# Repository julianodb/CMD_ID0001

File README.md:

CMD_ID0001_SW_1
===============
SW_1 : Health Manager implementation ofr test purposes. Uses de IEEE 11073 protocol (20601)

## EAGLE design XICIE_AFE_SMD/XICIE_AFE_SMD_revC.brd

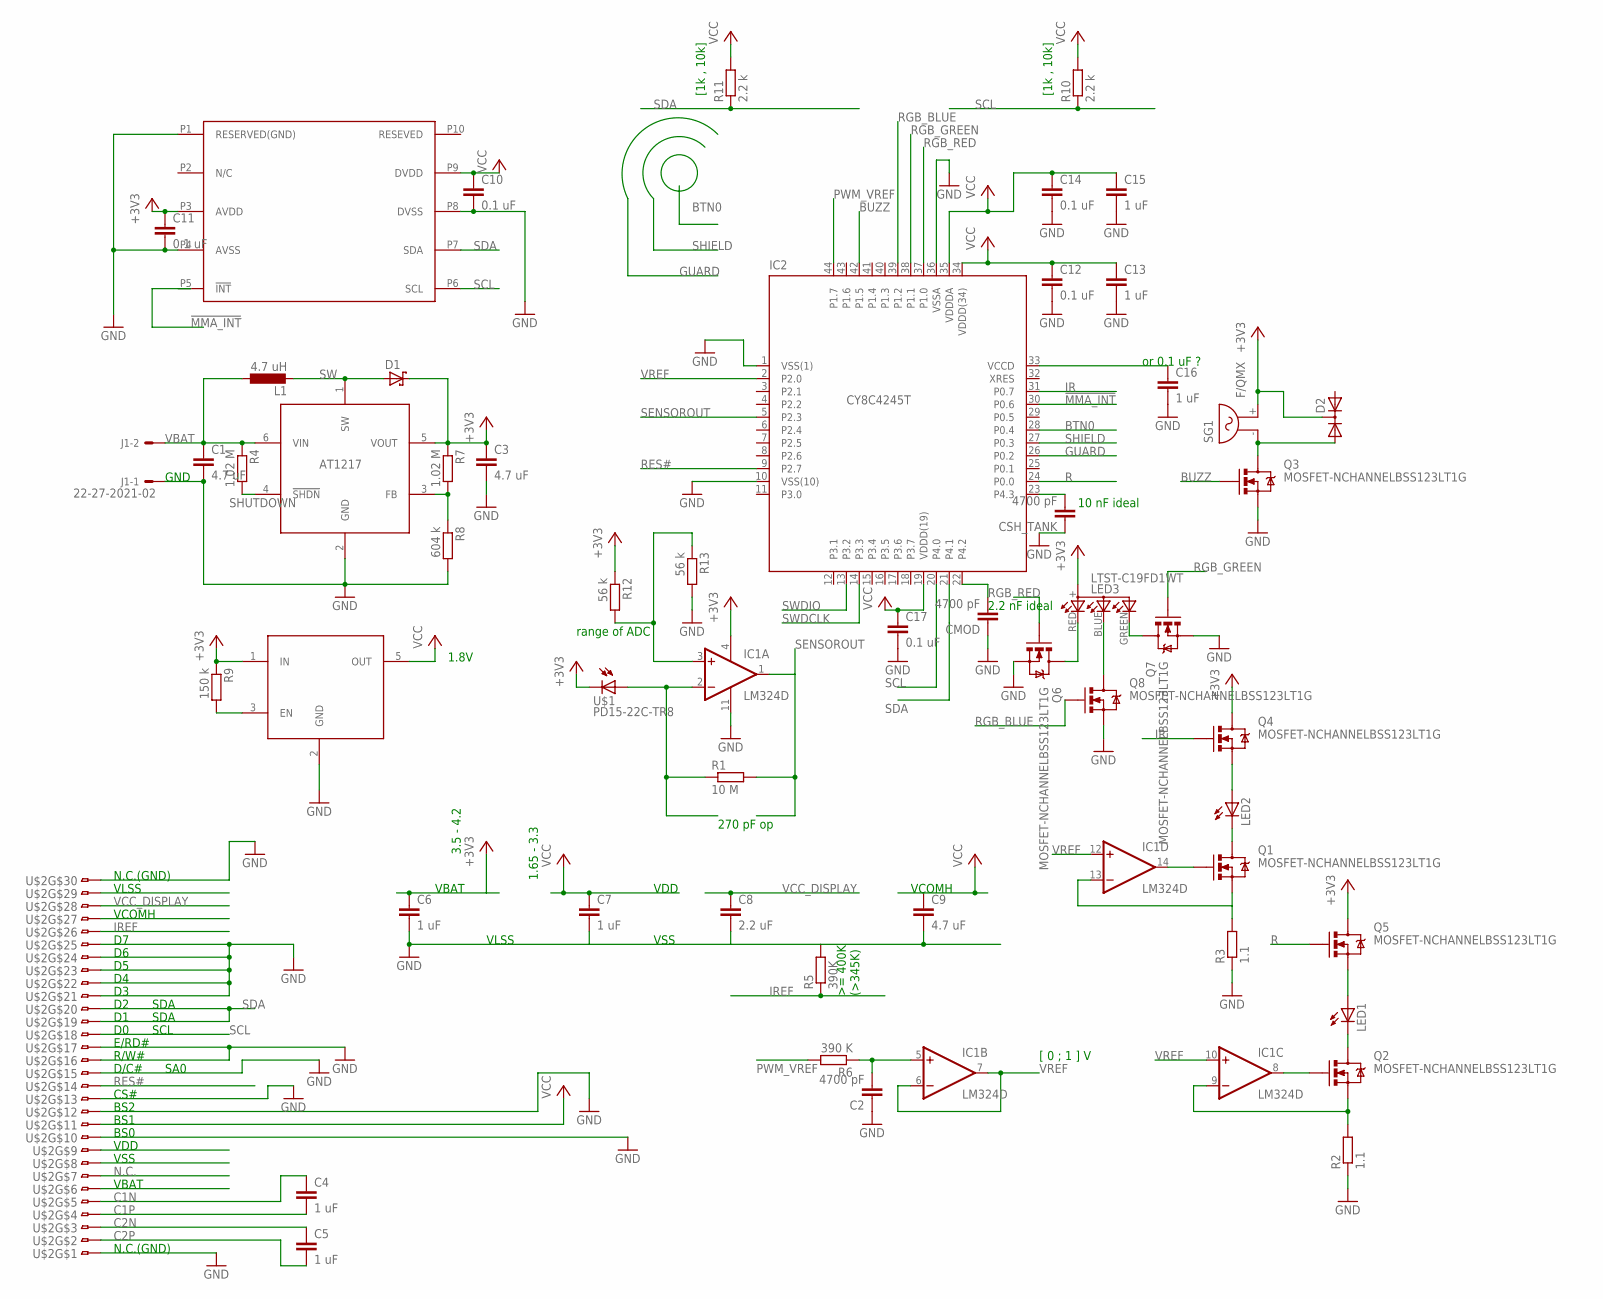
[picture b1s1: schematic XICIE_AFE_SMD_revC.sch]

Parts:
C1, C3, C9: 4.7 uF; C0603
C2: 4700 pF; C0402
C4, C5, C6, C7, C13, C15, C16: 1 uF; C0402
C8: 2.2 uF; C0603
C10, C11, C12, C14, C17: 0.1 uF; C0402
CMOD: 4700 pF; C0402
CSH_TANK: 4700 pF; C0402
D1: SCHOTTKY-DIODESMD; SMINI2-F5-B
D2: DIODE-2AC|CASOT23; SOT23
IC1: LM324D; SO14
IC2: CY8C4245T; TQFP44
IC3: AAT1217; SOT23-6
J1: 22-27-2021-02; 6410-02
L1: 4.7 uH; L2518
LED1, LED2: LED5MM
LED3: LTST-C19FD1WT; GM1WA55311A
Q1, Q2, Q3, Q4, Q5, Q6, Q7, Q8: MOSFET-NCHANNELBSS123LT1G; SOT23
R1: 10 M; R0402
R2, R3: 1.1; R0402
R4, R7: 1.02 M; R0805
R5: 390K; R0603
R6: 390 K; R0603
R8: 604 k; R0603
R9: 150 k; R0603
R10, R11: 2.2 k; R0402
R12, R13: 56 k; R0603
SG1: F/QMX
U$1: PD15-22C-TR8; PHOTO_SMD
U$2: ER-OLED0.96; FLEX0.7X30
U$3: AAT3221; SOT23-5
U$4: MMA7660FC; DFN10

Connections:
!MMA_INT: IC2.30 (P0.6)
+3V3: C3.1, C6.1, C11.1, D1.C, D2.3 (C), IC1.4 (V+), IC3.5 (VOUT), LED3.+ (A), Q4.3 (D), Q5.3 (D), R7.1, R9.1, R12.1, SG1.+ (2), U$1.CATHODE1 (C), U$1.CATHODE2 (C), U$2.P6, U$3.1 (IN), U$4.P3 (AVDD)
BTN0: IC2.28 (P0.4)
BUZZ: IC2.42 (P1.5), Q3.1 (G)
C1N: C4.1, U$2.P5
C1P: C4.2, U$2.P4
C2N: C5.1, U$2.P3
C2P: C5.2, U$2.P2
GND: C1.2, C2.1, C3.2, C6.2, C7.2, C8.2, C9.2, C10.2, C11.2, C12.2, C13.2, C14.2, C15.2, C16.2, C17.2, CMOD.1, CSH_TANK.1, IC1.11 (V-), IC2.1 (VSS(1)), IC2.10 (VSS(10)), IC2.36 (VSSA), IC3.2 (GND), J1.1, Q3.2 (S), Q6.2 (S), Q7.2 (S), Q8.2 (S), R2.1, R3.1, R5.2, R8.2, R13.2, U$2.P1, U$2.P8, U$2.P10, U$2.P12, U$2.P13, U$2.P15, U$2.P16, U$2.P17, U$2.P21, U$2.P22, U$2.P23, U$2.P24, U$2.P25, U$2.P29, U$2.P30, U$3.2 (GND), U$4.P1 (RESERVED(GND)), U$4.P4 (AVSS), U$4.P8 (DVSS)
GUARD: IC2.26 (P0.2)
IR: IC2.31 (P0.7), Q4.1 (G)
IREF: R5.1, U$2.P26
unnamed: IC1.2 (-IN), R1.1, U$1.ANODE1 (A), U$1.ANODE2 (A)
unnamed: IC1.9 (-IN), Q2.2 (S), R2.2
unnamed: LED2.A, Q4.2 (S)
unnamed: LED1.K (C), Q2.3 (D)
unnamed: LED2.K (C), Q1.3 (D)
unnamed: IC1.8 (OUT), Q2.1 (G)
unnamed: IC1.13 (-IN), Q1.2 (S), R3.2
unnamed: C2.2, IC1.5 (+IN), R6.1
unnamed: C16.1, IC2.33 (VCCD)
unnamed: IC3.3 (FB), R7.2, R8.1
unnamed: D2.1 (A1), Q3.3 (D), SG1.- (1)
unnamed: R9.2, U$3.3 (EN)
unnamed: IC1.3 (+IN), R12.2, R13.1
unnamed: LED1.A, Q5.2 (S)
unnamed: LED3.RED (CRED), Q6.3 (D)
unnamed: LED3.BLUE (CBLUE), Q8.3 (D)
unnamed: IC1.14 (OUT), Q1.1 (G)
unnamed: LED3.GREEN (CGREEN), Q7.3 (D)
unnamed: CMOD.2, IC2.22 (P4.2)
unnamed: CSH_TANK.2, IC2.23 (P4.3)
N.C.: U$2.P7
P2.2: IC2.4 (P2.2)
P2.6: IC2.8 (P2.6)
P3.6: IC2.17 (P3.6)
PWM_VREF: IC2.44 (P1.7), R6.2
R: IC2.24 (P0.0), Q5.1 (G)
RES#: IC2.9 (P2.7), U$2.P14
RGB_BLUE: IC2.39 (P1.2), Q8.1 (G)
RGB_GREEN: IC2.38 (P1.1), Q7.1 (G)
RGB_RED: IC2.37 (P1.0), Q6.1 (G)
SCL: IC2.20 (P4.0), R10.1, U$2.P18, U$4.P6 (SCL)
SDA: IC2.21 (P4.1), R11.1, U$2.P19, U$2.P20, U$4.P7 (SDA)
SENSOROUT: IC1.1 (OUT), IC2.5 (P2.3), R1.2
SHIELD: IC2.27 (P0.3)
SHUTDOWN: IC3.4 (!SHDN), R4.2
SW: D1.A, IC3.1 (SW), L1.2
SWDCLK: IC2.14 (P3.3)
SWDIO: IC2.13 (P3.2)
VBAT: C1.1, IC3.6 (VIN), J1.2, L1.1, R4.1
VCC: C7.1, C9.1, C10.1, C12.1, C13.1, C14.1, C15.1, C17.1, IC2.19 (VDDD(19)), IC2.34 (VDDD(34)), IC2.35 (VDDDA), R10.2, R11.2, U$2.P9, U$2.P11, U$2.P27, U$3.5 (OUT), U$4.P9 (DVDD)
VCC_DISPLAY: C8.1, U$2.P28
VREF: IC1.6 (-IN), IC1.7 (OUT), IC1.10 (+IN), IC1.12 (+IN), IC2.2 (P2.0)

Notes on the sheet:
270 pF op
GND
BS0
BS1
BS2
N.C.(GND)
VBAT
VSS
VLSS
VCOMH
3.5 - 4.2
1.65 - 3.3
VDD
1.8V
SA0
SDA
SCL
[1k , 10k]
range of ADC
[ 0 ; 1 ] V
CS#
2.2 nF ideal
10 nF ideal
D/C#
E/RD#
R/W#
or 0.1 uF ?

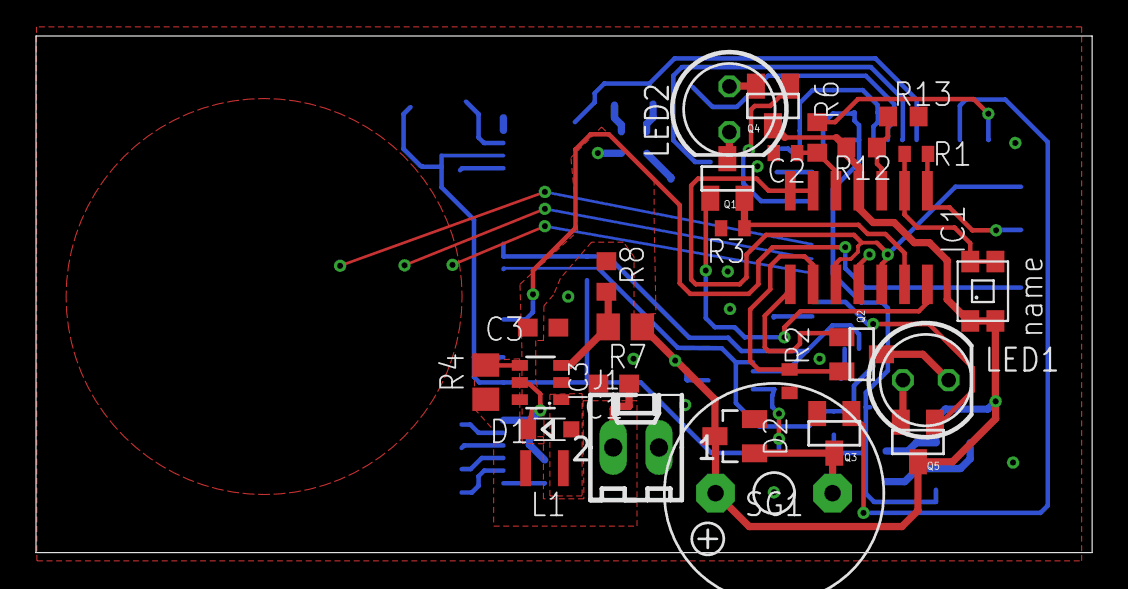
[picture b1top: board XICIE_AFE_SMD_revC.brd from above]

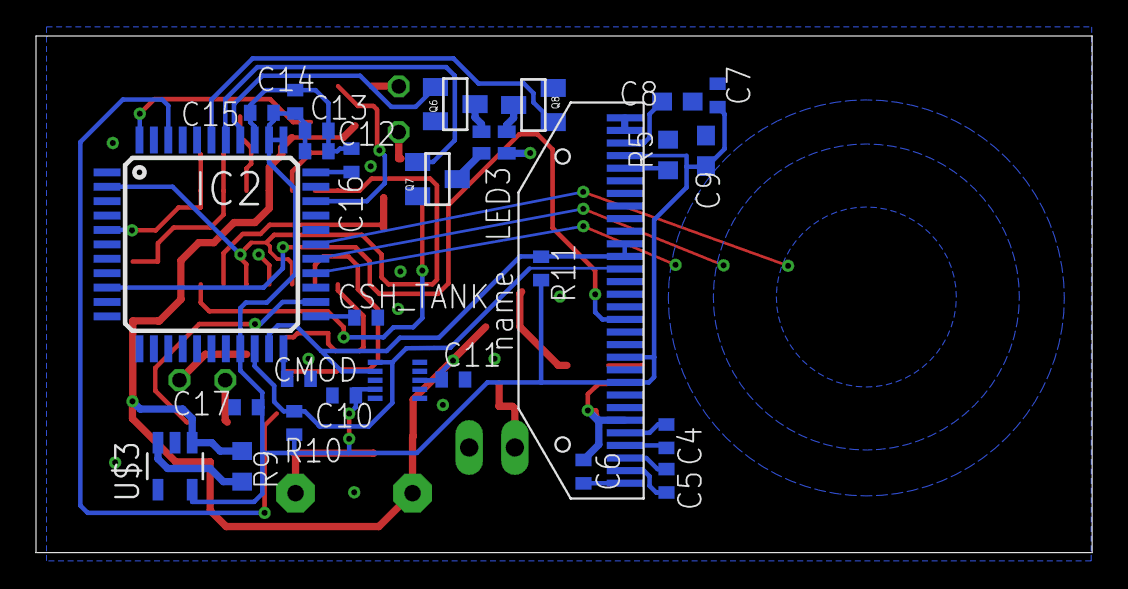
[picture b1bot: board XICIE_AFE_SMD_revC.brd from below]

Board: 2 copper layers, 58.7 x 28.7 mm, 55 parts (28 on the bottom side), 44 nets.

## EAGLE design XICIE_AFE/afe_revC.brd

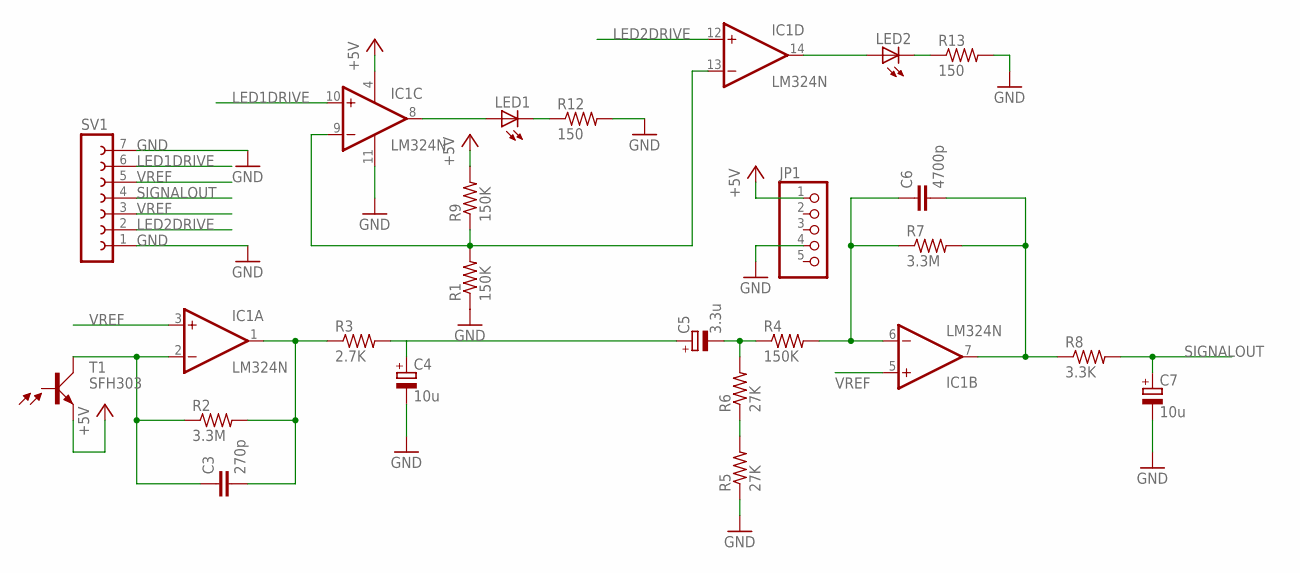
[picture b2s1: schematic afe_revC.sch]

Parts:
C3: 270p; C050-024X044
C4, C7: 10u; E2,5-5
C5: 3.3u; E2,5-5
C6: 4700p; C050-024X044
IC1: LM324N; DIL14
JP1: PINHD-1X5; 1X05
LED1, LED2: LED5MM
R1, R4, R9: 150K; 0207/10
R2, R7: 3.3M; 0207/10
R3: 2.7K; 0207/10
R5, R6: 27K; 0207/10
R8: 3.3K; 0207/10
R12, R13: 150; 0207/10
SV1: FE07-1; FE07
T1: SFH303

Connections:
+5V: IC1.4 (V+), JP1.1, R9.2, T1.1 (E)
GND: C4.-, C7.-, IC1.11 (V-), JP1.4, R1.1, R5.1, R12.2, R13.2, SV1.1, SV1.7
LED1DRIVE: IC1.10 (+IN), SV1.6
LED2DRIVE: IC1.12 (+IN), SV1.2
unnamed: C3.2, IC1.1 (OUT), R2.2, R3.1
unnamed: C3.1, IC1.2 (-IN), R2.1, T1.2 (C)
unnamed: C4.+, C5.+, R3.2
unnamed: C5.-, R4.1, R6.2
unnamed: R5.2, R6.1
unnamed: C6.1, IC1.6 (-IN), R4.2, R7.1
unnamed: C6.2, IC1.7 (OUT), R7.2, R8.1
unnamed: IC1.9 (-IN), IC1.13 (-IN), R1.2, R9.1
unnamed: LED1.K (C), R12.1
unnamed: LED2.K (C), R13.1
unnamed: IC1.8 (OUT), LED1.A
unnamed: IC1.14 (OUT), LED2.A
SIGNALOUT: C7.+, R8.2, SV1.4
VREF: IC1.3 (+IN), IC1.5 (+IN), SV1.3, SV1.5

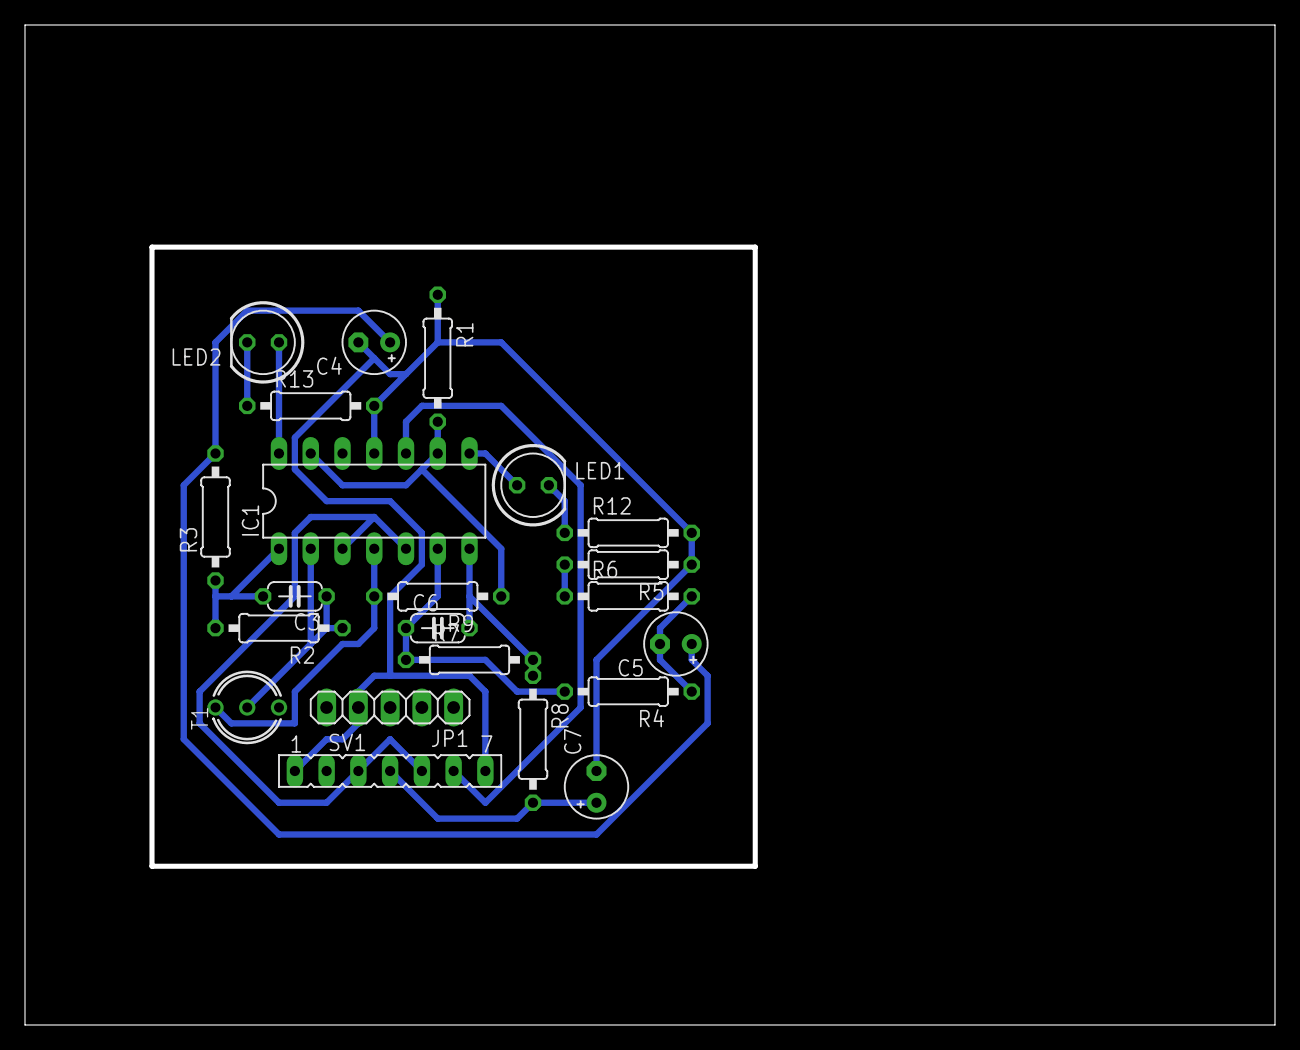
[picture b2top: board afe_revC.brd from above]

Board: 2 copper layers, 99.6 x 79.6 mm, 22 parts (0 on the bottom side), 18 nets.

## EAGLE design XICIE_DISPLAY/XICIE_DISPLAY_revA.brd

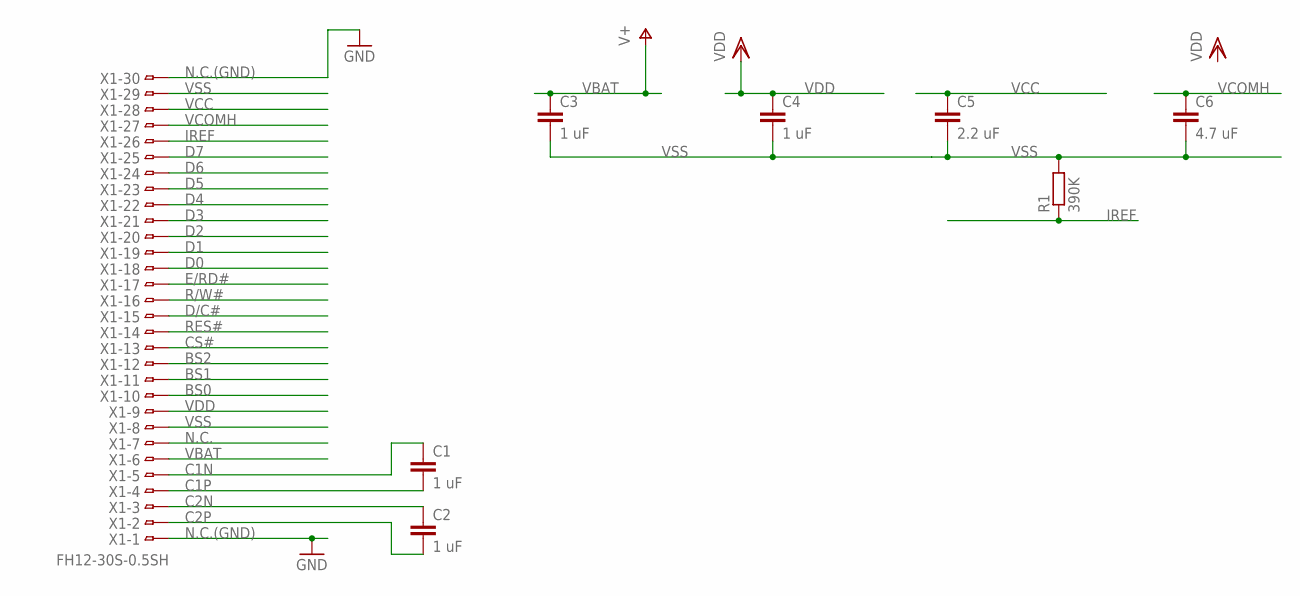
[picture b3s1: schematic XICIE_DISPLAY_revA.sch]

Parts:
C1, C2, C3, C4: 1 uF; C0402
C5: 2.2 uF; C0603
C6: 4.7 uF; C0603
R1: 390K; R0603
X1: FH12-30S-0.5SH

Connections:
BS0: X1.10
BS1: X1.11
BS2: X1.12
C1N: C1.1, X1.5
C1P: C1.2, X1.4
C2N: C2.1, X1.3
C2P: C2.2, X1.2
CS#: X1.13
D0: X1.18
D1: X1.19
D2: X1.20
D3: X1.21
D4: X1.22
D5: X1.23
D6: X1.24
D7: X1.25
D/C#: X1.15
E/RD#: X1.17
IREF: R1.1, X1.26
N.C.: X1.7
N.C.(GND): X1.1, X1.30
R/W#: X1.16
RES#: X1.14
VBAT: C3.1, X1.6
VCC: C5.1, X1.28
VCOMH: C6.1, X1.27
VDD: C4.1, X1.9
VSS: C3.2, C4.2, C5.2, C6.2, R1.2, X1.8, X1.29

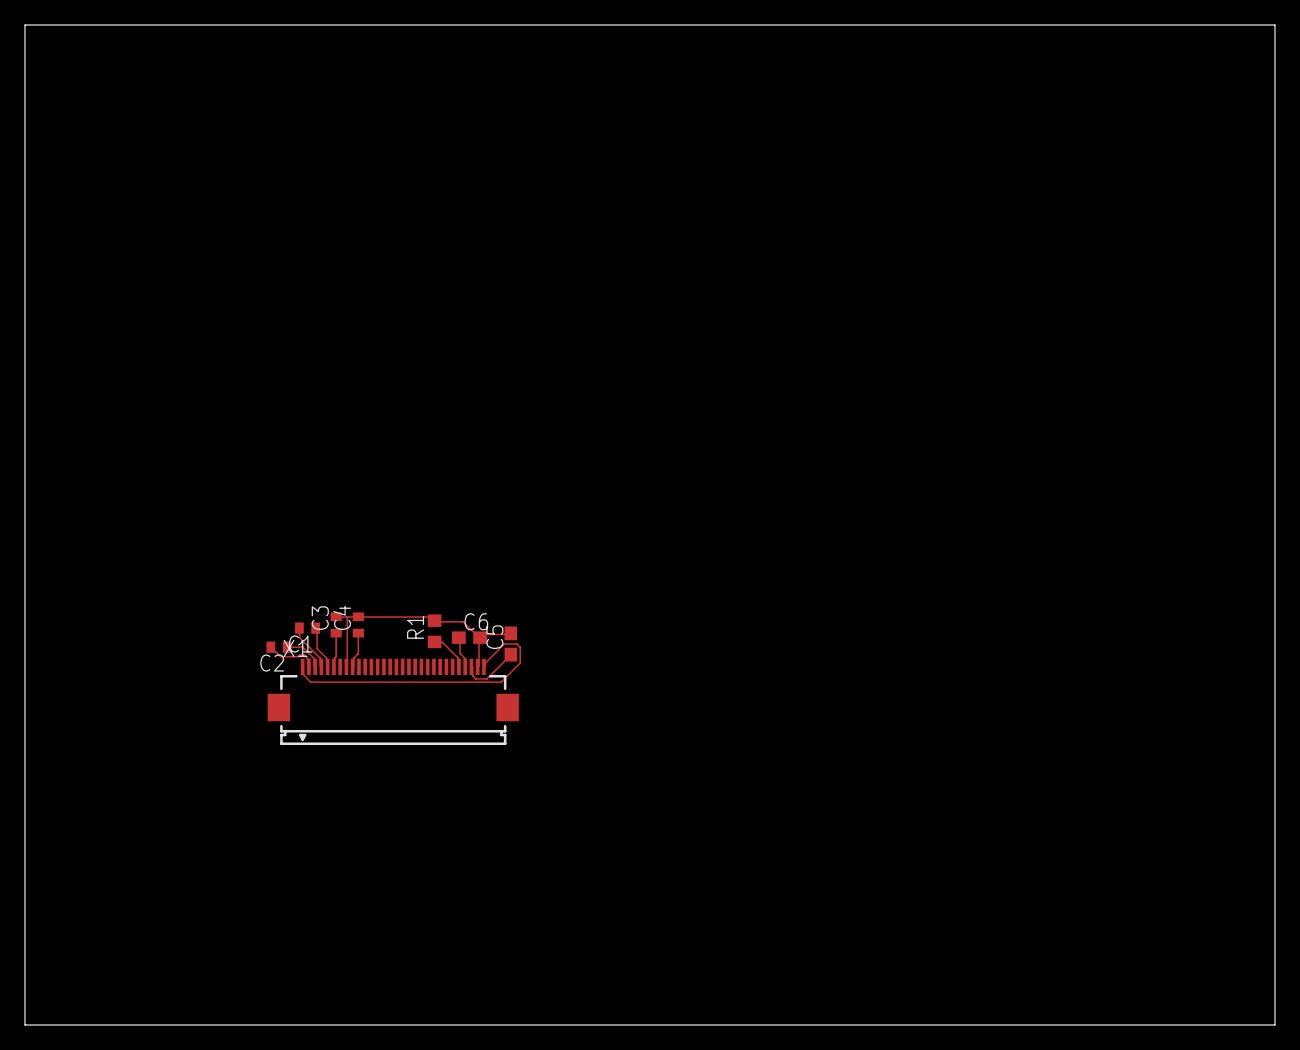
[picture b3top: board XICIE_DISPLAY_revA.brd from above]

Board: 2 copper layers, 100.0 x 80.0 mm, 8 parts (0 on the bottom side), 11 nets.

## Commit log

2014-02-09 Added brief description of the project
    The project will implement a health manager based on IEEE 11073 protocols
    for testing purposes. It shall also be able to display the information it
    gets.
2014-02-11 Added first version of AFE board
    The board implements the best performance circuit tested.
2014-02-11 Added second version of AFE board
    The second version fixes some components sizes, changes the reference of the notch filter to VREF and add the signal SIGNALOUT to the female header.
2014-02-11 Added prelimary version of the AFE SW
2014-02-24 Added first version of Proto02 program
    Proto02 functions as a simple ADC/logger to be used for developing
    purposes
2014-02-24 Implemented led_toggle and added led_toggle(GREEN_LED) on main
2014-02-24 Cleaned board_stellaris.c code
2014-02-24 Reimplemented uart_printf as a pointer to UARTprintf
2014-02-26 Added PWM basic support
    The PWM uses the Wide Timer 2 as timer and PD0 as output. There is also a
    simple function to scale the pwm duty cycle (pwm_set_duty).
2014-02-26 Changed data types to default C99 (stdint.h)
2014-03-06 Added third revision of AFE (revC)
    Increased distances to avoid short-circuits. This revision was made
    with Eagle Light for windows 6.5.0, wich caused some changes in the
    project file.
2014-03-19 Minor changes in AFE revC and added DISPLAY board
2014-03-23 Added octave model for the filter being used
2014-04-06 First attempt on smd components for AFE
2014-04-08 Minor changes in afe_smd
2014-04-09 Added PSoc IC and boost converter
2014-04-11 PCB Layoutd
2014-04-11 Finished layout
2014-04-11 Reduced outline
2014-04-11 Trying to merge display
2014-04-16 Intermediate commit to change computers...
2014-04-16 Added all components and connections
    Still in doubt if BUZZ driver will use a resistor,
    and if TIA should have a capacitor.
2014-04-17 Finished layout for first proposal
2014-04-18 Increased clearance for better manufacturing
2014-04-30 Added revision B of board
    Included MMA interrupt and bypass capacitors for psoc.
2014-06-13 Finished rev B of XICIE_AFE_SMD
    Many things added, like button, buzzer, RGB
    led. Placing improved manually. Still missing
    connection to program PSoC4.

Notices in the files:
parts and their libraries:
SparkFun-DiscreteSemi: Licensing: Creative Commons ShareAlike 4.0 International - https://creativecommons.org/licenses/by-sa/4.0
